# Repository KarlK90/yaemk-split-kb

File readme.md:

<!--
SPDX-FileCopyrightText: 2021 Stefan Kerkmann <karlk90@pm.me>

SPDX-License-Identifier: CC-BY-SA-4.0
-->

# Yet Another Ergonomic Mechanical Keyboard

[![REUSE status](
    https://api.reuse.software/badge/github.com/KarlK90/yaemk-split-kb)](
    https://api.reuse.software/info/github.com/KarlK90/yaemk-split-kb)

# [>>> VISIT THE WEBSITE <<<](https://karlk90.github.io/yaemk-split-kb/)

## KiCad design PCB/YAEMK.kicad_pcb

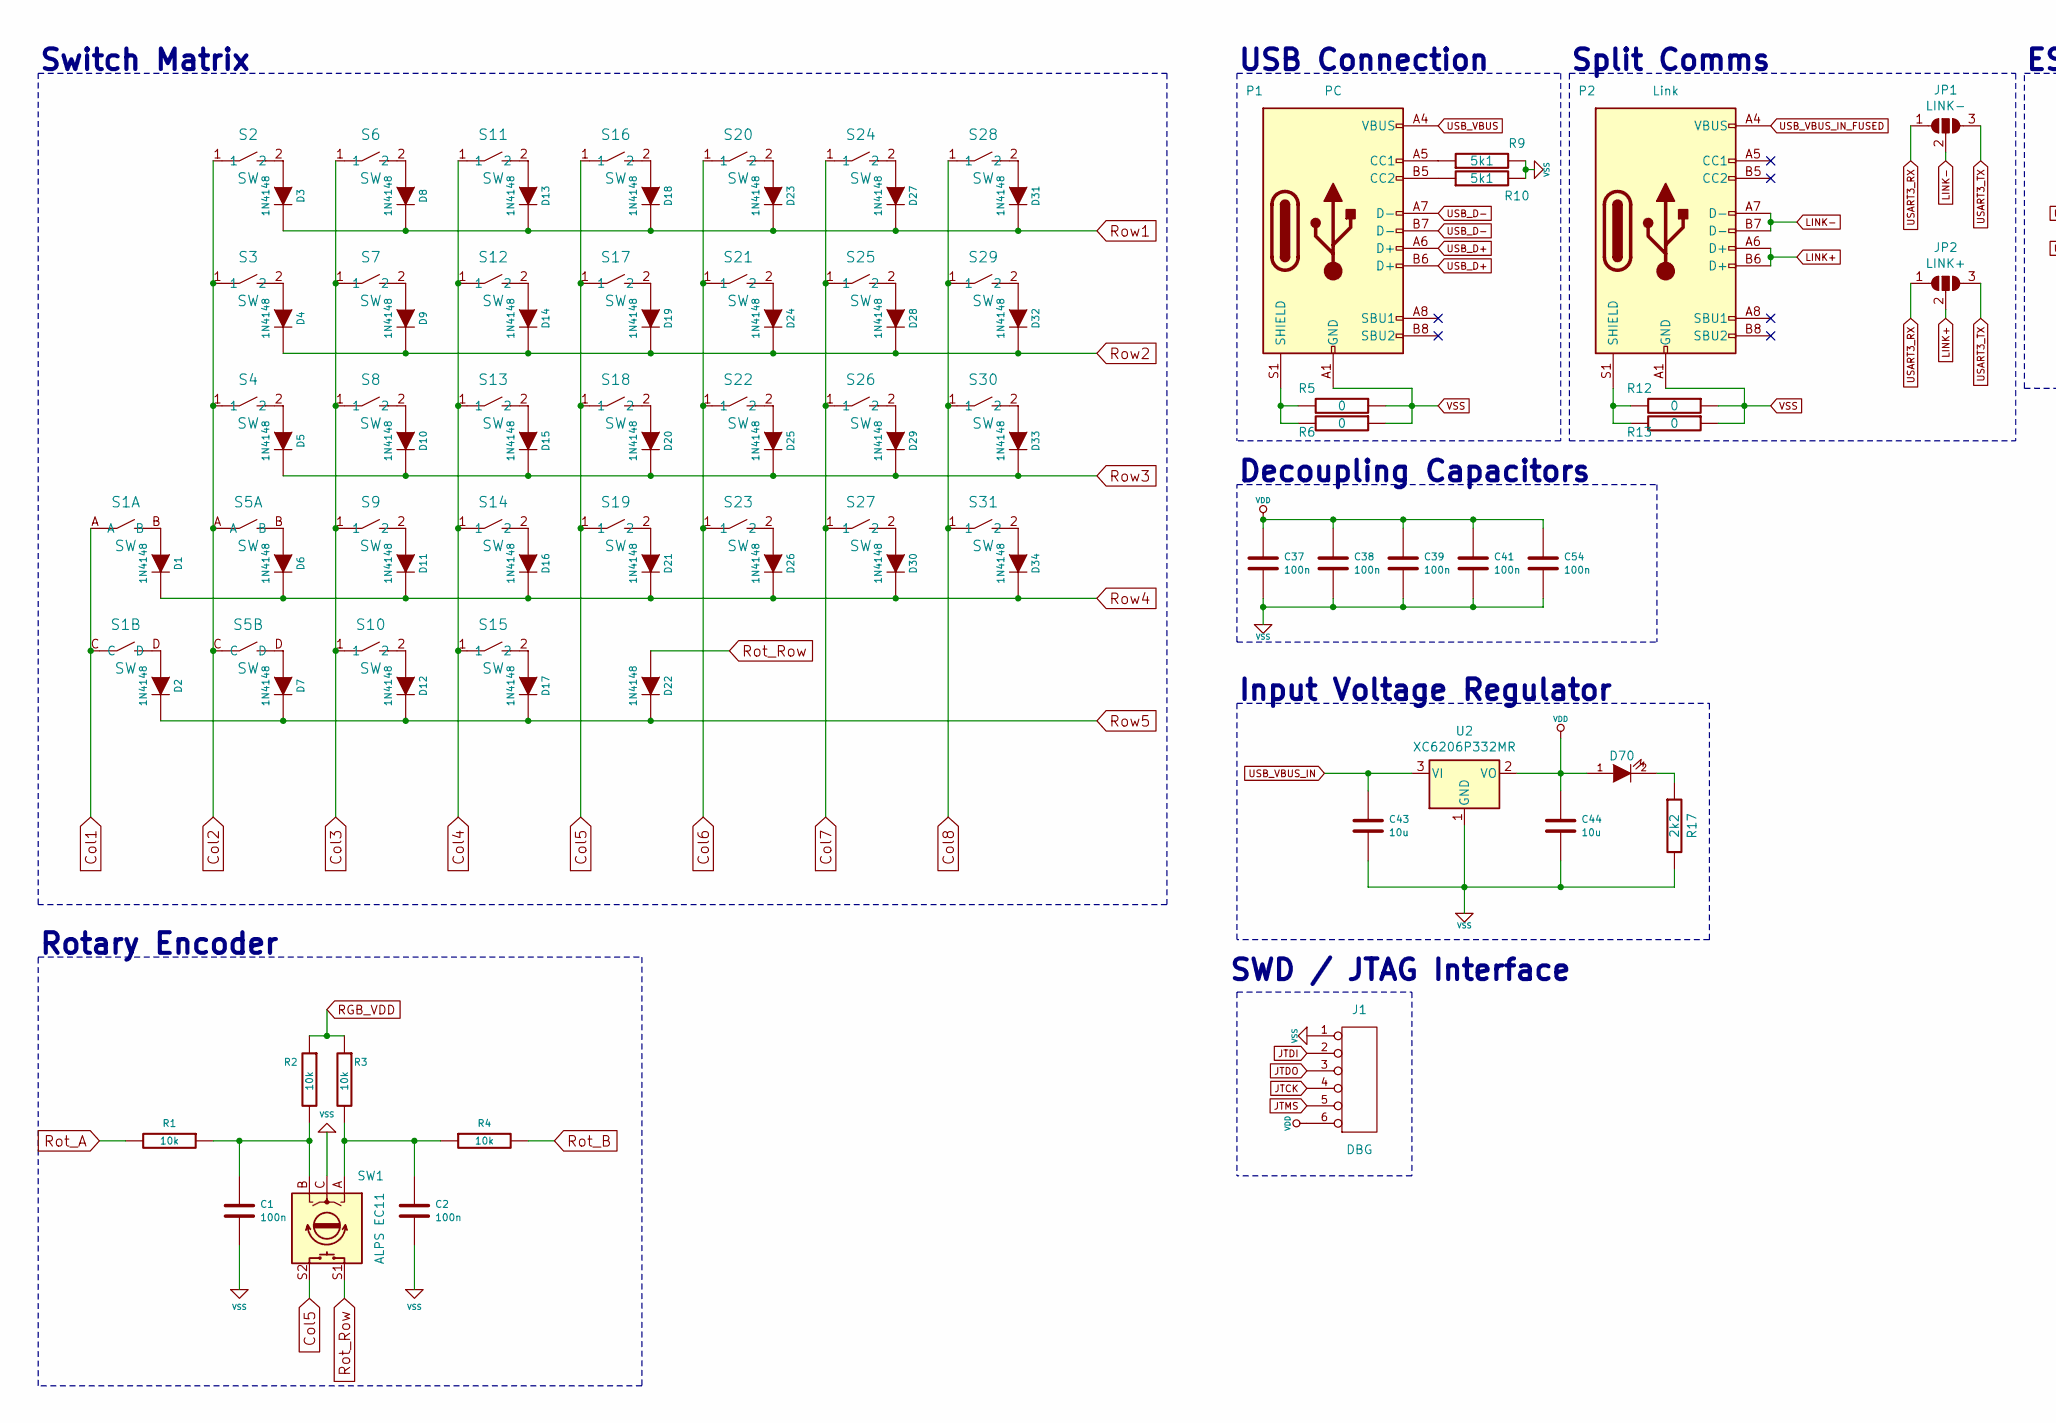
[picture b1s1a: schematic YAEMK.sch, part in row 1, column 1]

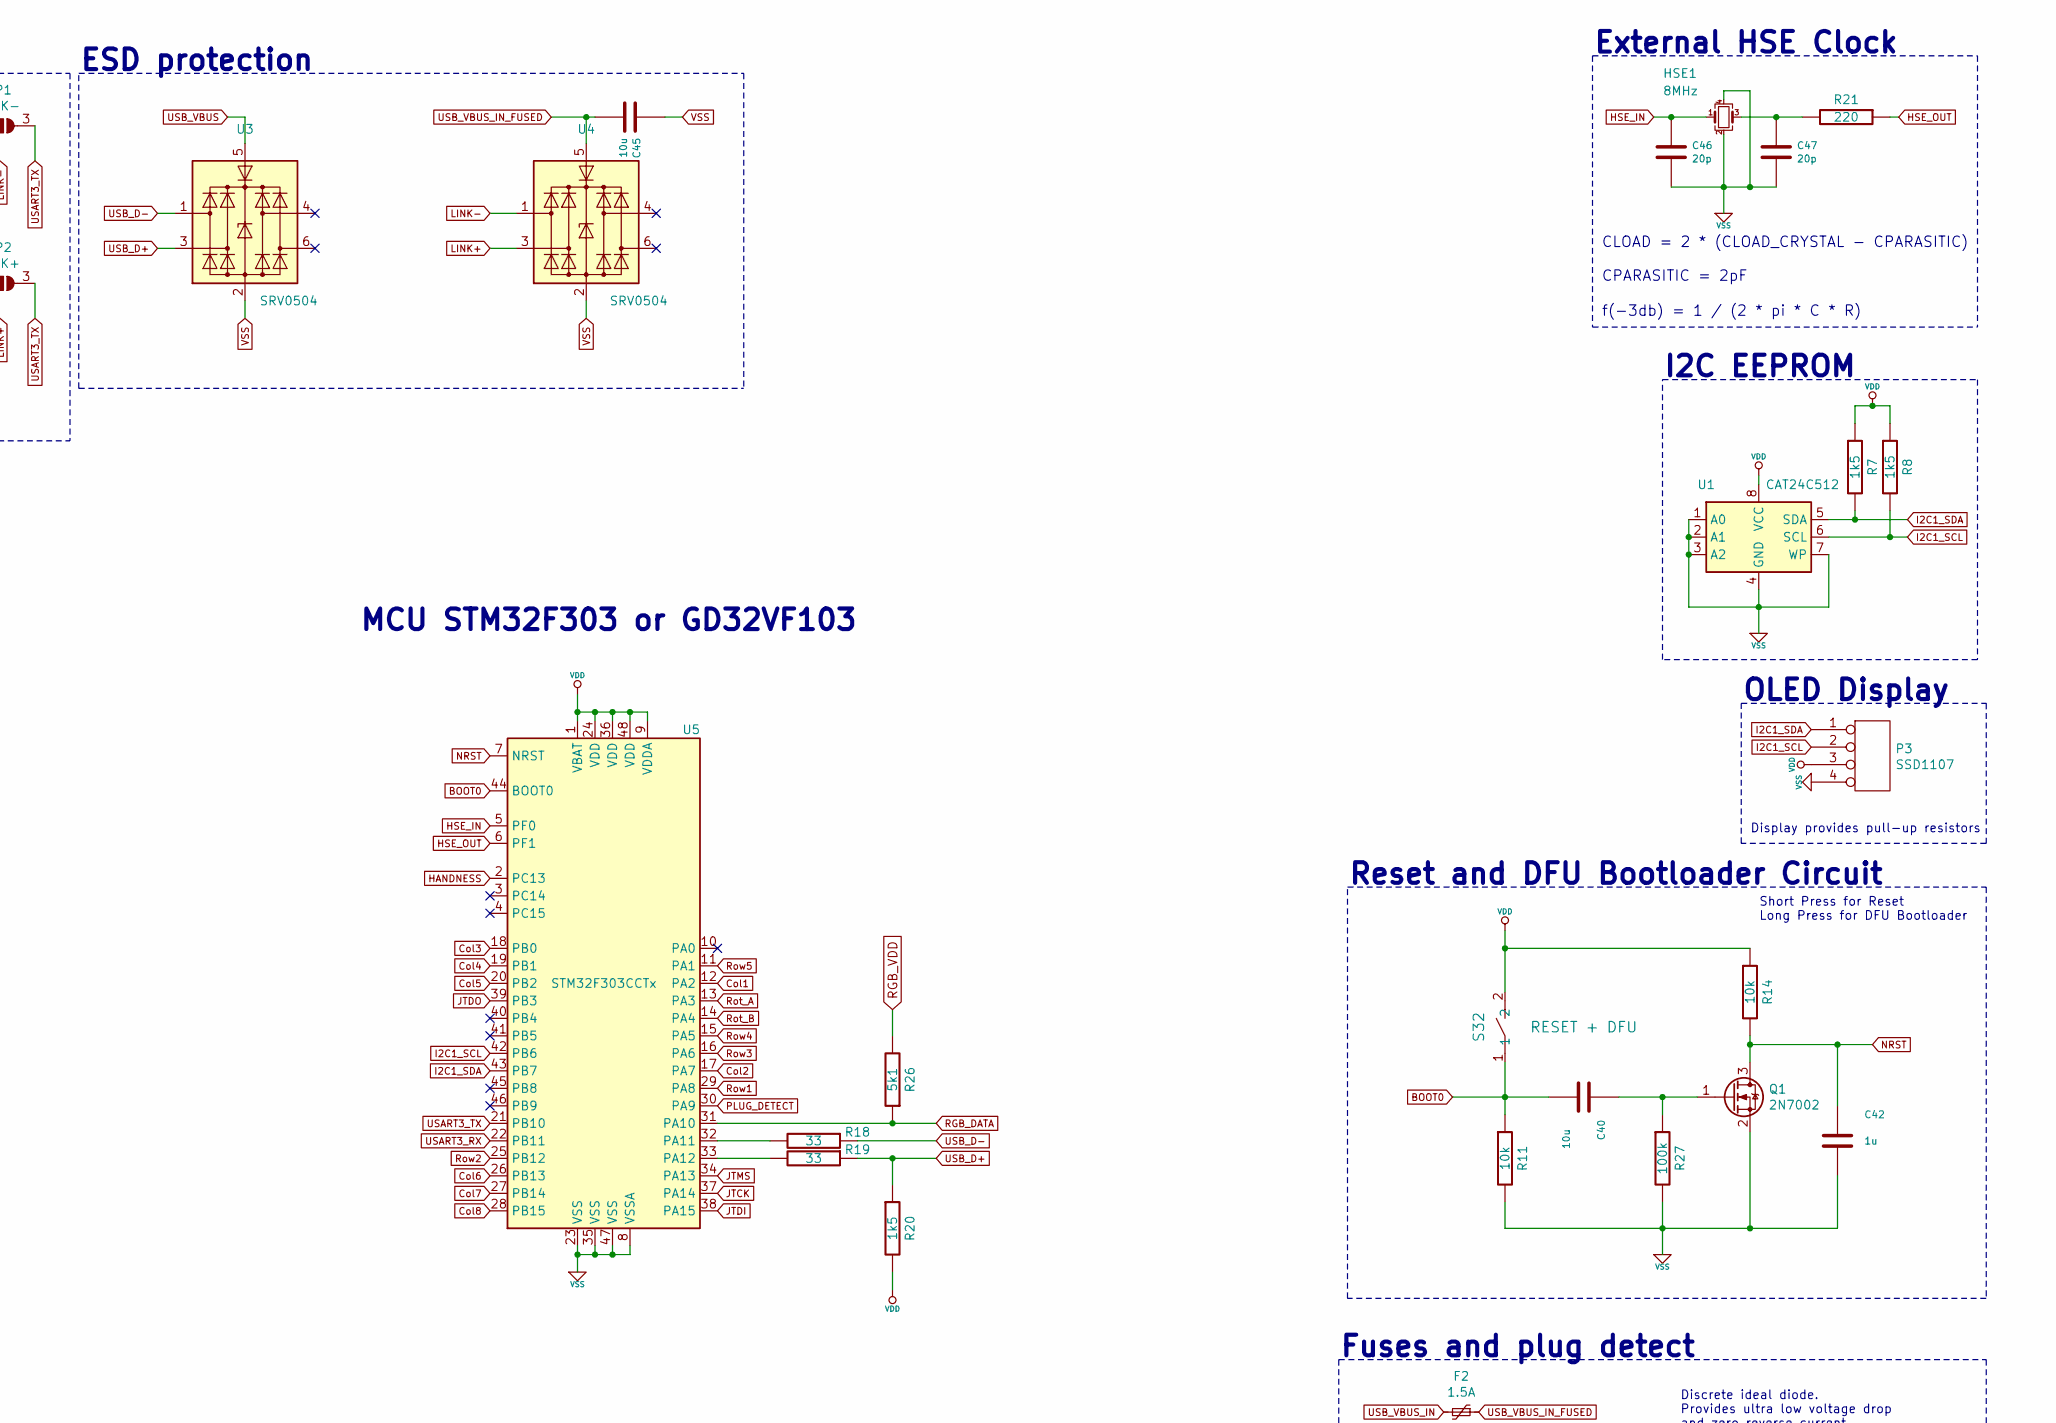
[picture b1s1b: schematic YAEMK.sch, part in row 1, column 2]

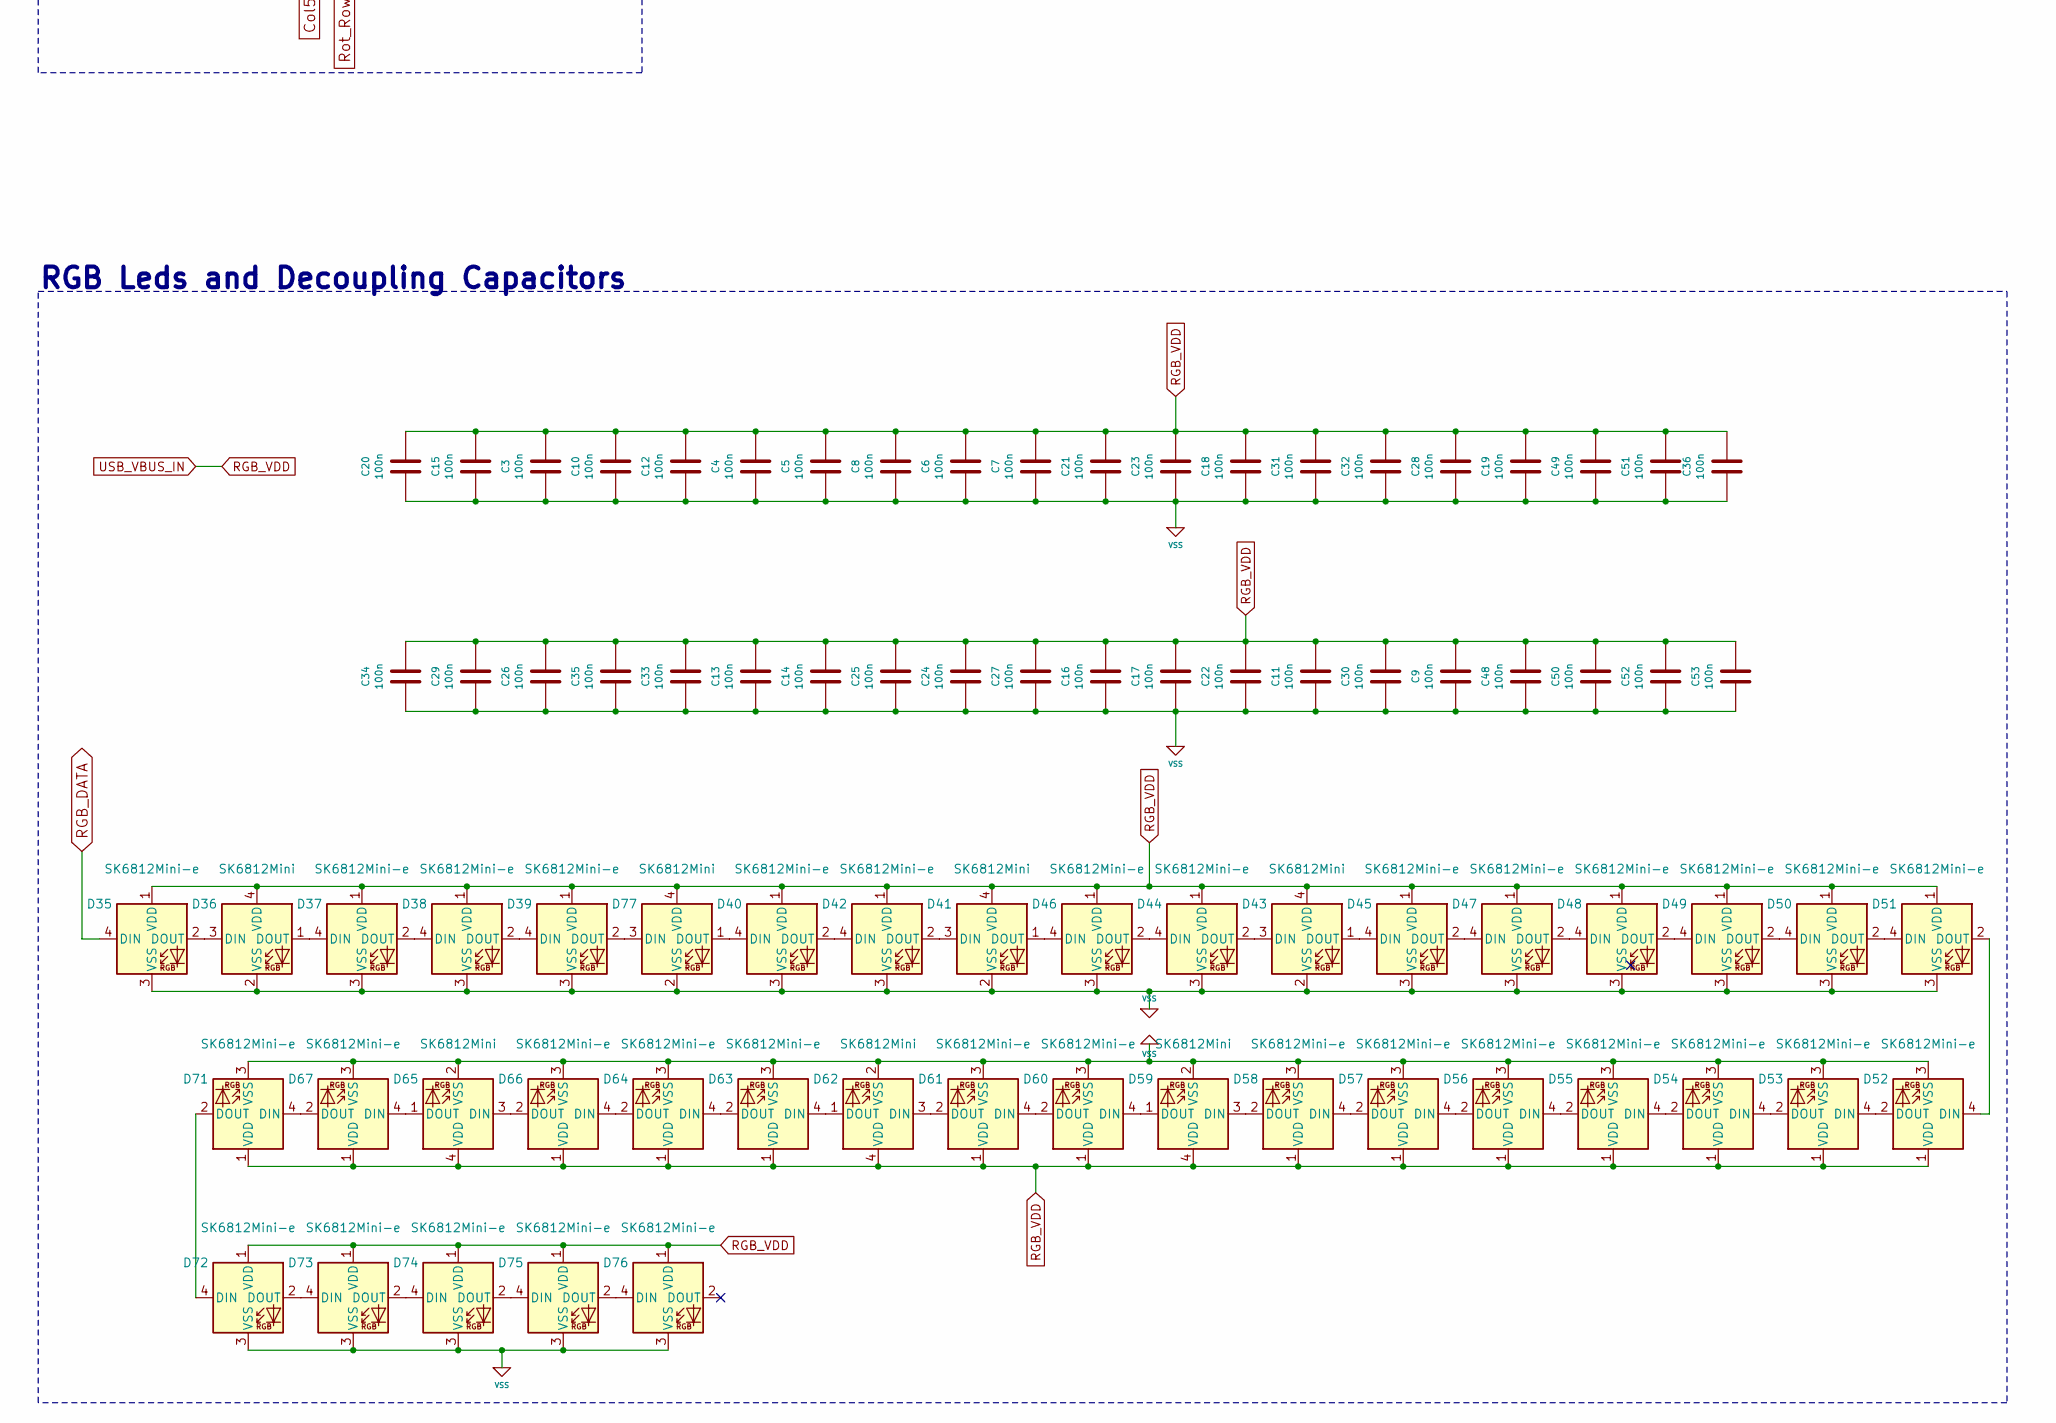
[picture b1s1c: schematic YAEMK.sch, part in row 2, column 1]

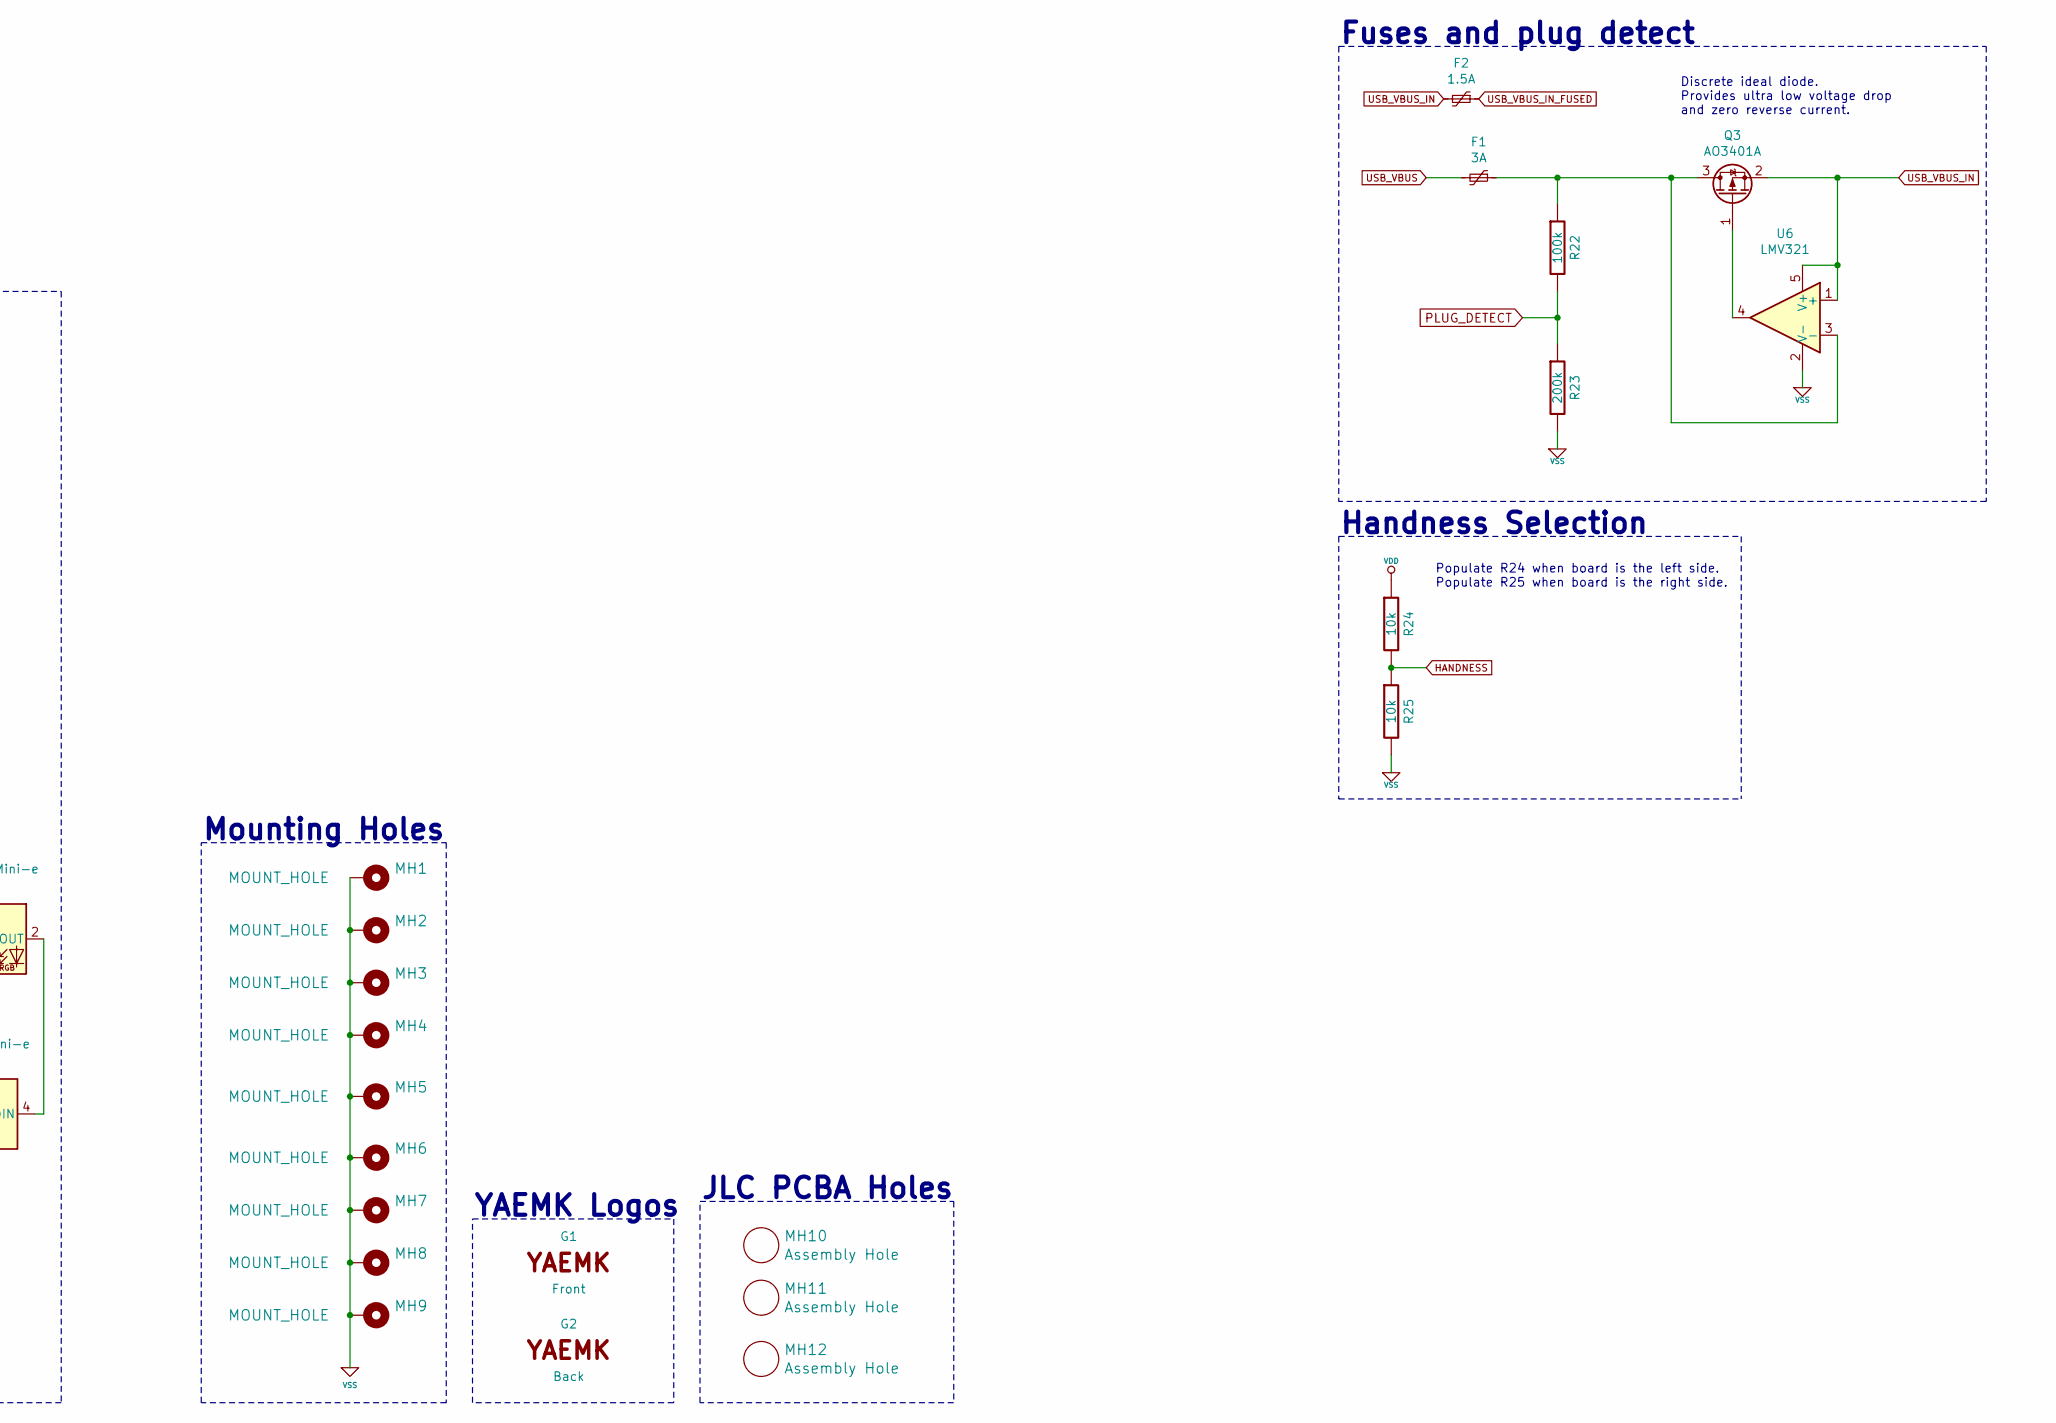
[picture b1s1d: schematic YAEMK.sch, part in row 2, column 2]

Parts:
C1, C2, C3, C4, C5, C6, C7, C8, C9, C10, C11, C12, C13, C14, C15, C16, C17, C18, C19, C20, C21, C22, C23, C24, C25, C26, C27, C28, C29, C30, C31, C32, C33, C34, C35, C36, C37, C38, C39, C41, C48, C49, C50, C51, C52, C53, C54: 100n; SMD-0603; LCSC Part C14663
C40, C43, C44, C45: 10u; SMD-0603; LCSC Part C19702
C42: 1u; SMD-0603; LCSC Part C15849
C46, C47: 20p; SMD-0603; LCSC Part C1648
D1, D2, D3, D4, D5, D6, D7, D8, D9, D10, D11, D12, D13, D14, D15, D16, D17, D18, D19, D20, D21, D22, D23, D24, D25, D26, D27, D28, D29, D30, D31, D32, D33, D34: 1N4148; D_SOD-123; LCSC Part C81598
D35, D37, D38, D39, D40, D42, D44, D45, D46, D47, D48, D49, D50, D51, D52, D53, D54, D55, D56, D57, D58, D60, D61, D63, D64, D66, D67, D71, D72, D73, D74, D75, D76: SK6812Mini-e; SK6812_mini_e_flipable; JLCPCB BOM 0
D36, D41, D43, D59, D62, D65, D77: SK6812Mini; SK6812_mini_flipable; JLCPCB BOM 0
D70: LED; LED-0603_flipable; LCSC Part C268294
F1: 3A; Fuse_1206_3216Metric; LCSC Part C70085
F2: 1.5A; Fuse_1206_3216Metric; LCSC Part C70081
G1: Front; LOGO; JLCPCB BOM 0
G2: Back; LOGO; JLCPCB BOM 0
HSE1: 8MHz; Crystal_SMD_3225-4Pin_3.2x2.5mm; LCSC Part C403948
J1: DBG; PinHeader_1x06_P2.54mm_Horizontal; LCSC Part C376124
JP1: LINK-; SOLDER_JUMPER_3; JLCPCB BOM 0
JP2: LINK+; SOLDER_JUMPER_3; JLCPCB BOM 0
MH1, MH2, MH3, MH4, MH5, MH6, MH7, MH8, MH9: MOUNT_HOLE; MountingHole_2.2mm_M2_Pad_Via; JLCPCB BOM 0
MH10, MH11, MH12: Assembly Hole; JLC_SMT_Assembly_Hole; JLCPCB BOM 0
P1: PC; USB_C_Receptacle_MUP_U22401; LCSC Part C168688
P2: Link; USB_C_Receptacle_MUP_U22401; LCSC Part C168688
P3: SSD1107; SSD1107_DISPLAY; LCSC Part C358718
Q1: 2N7002; SOT-23; LCSC Part C8545
Q3: AO3401A; SOT-23; LCSC Part C15127
R1, R2, R3, R4, R11, R14, R24, R25: 10k; SMD-0603; LCSC Part C25804
R5, R6, R12, R13: 0; SMD-0603; LCSC Part C21189
R7, R8, R20: 1k5; SMD-0603; LCSC Part C22843
R9, R10, R26: 5k1; SMD-0603; LCSC Part C23186
R17: 2k2; SMD-0603; LCSC Part C4190
R18, R19: 33; SMD-0603; LCSC Part C23140
R21: 220; SMD-0603; LCSC Part C22962
R22, R27: 100k; SMD-0603; LCSC Part C25803
R23: 200k; SMD-0603; LCSC Part C25811
S1, S5: SW; MX_KAILH_SOCKET_2U_2X1U; JLCPCB BOM 0
S2, S3, S4, S6, S7, S8, S9, S10, S11, S12, S13, S14, S15, S16, S17, S18, S19, S20, S21, S22, S23, S24, S25, S26, S27, S28, S29, S30, S31: SW; MX_KAILH_SOCKET_1U; JLCPCB BOM 0
S32: RESET + DFU; SMD_Tacticle_Switch_TS24CA_flipable; LCSC Part C393942
SW1: ALPS EC11; RotaryEncoder_Alps_EC11E-Switch_Vertical_H20mm; LCSC Part C370986
U1: CAT24C512; TSSOP-8_4.4x3mm_P0.65mm; LCSC Part C56096
U2: XC6206P332MR; SOT-23; LCSC Part C5446
U3, U4: SRV0504; SOT-23-6; JLCPCB BOM 1
U5: STM32F303CCTx; LQFP-48_7x7mm_P0.5mm; LCSC Part C81523
U6: LMV321; SOT-23-5; JLCPCB BOM 1

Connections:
BOOT0: C40.1, R11.1, S32.1, U5.44 (BOOT0)
Col1: S1.A, S1.C, U5.12 (PA2)
Col2: S2.1, S3.1, S4.1, S5.A, S5.C, U5.17 (PA7)
Col3: S6.1, S7.1, S8.1, S9.1, S10.1, U5.18 (PB0)
Col4: S11.1, S12.1, S13.1, S14.1, S15.1, U5.19 (PB1)
Col5: S16.1, S17.1, S18.1, S19.1, SW1.S2, U5.20 (PB2)
Col6: S20.1, S21.1, S22.1, S23.1, U5.26 (PB13)
Col7: S24.1, S25.1, S26.1, S27.1, U5.27 (PB14)
Col8: S28.1, S29.1, S30.1, S31.1, U5.28 (PB15)
HANDNESS: R24.2, R25.1, U5.2 (PC13)
HSE_IN: C46.1, HSE1.1, U5.5 (PF0)
HSE_OUT: R21.1, U5.6 (PF1)
I2C1_SCL: P3.2, R8.2, U1.6 (SCL), U5.42 (PB6)
I2C1_SDA: P3.1, R7.2, U1.5 (SDA), U5.43 (PB7)
JTCK: J1.4, U5.37 (PA14)
JTDI: J1.2, U5.38 (PA15)
JTDO: J1.3, U5.39 (PB3)
JTMS: J1.5, U5.34 (PA13)
LINK+: JP2.2 (C), P2.A6 (D+), P2.B6 (D+), U4.3 (I/O2)
LINK-: JP1.2 (C), P2.A7 (D-), P2.B7 (D-), U4.1 (I/O1)
NRST: C42.1, Q1.3 (D), R14.2, U5.7 (NRST)
unnamed: C1.1, R1.1, R2.2, SW1.B
unnamed: C2.1, R3.2, R4.1, SW1.A
unnamed: C40.2, Q1.1 (G), R27.1
unnamed: C47.1, HSE1.3, R21.2
unnamed: D1.2 (A), S1.B
unnamed: D2.2 (A), S1.D
unnamed: D3.2 (A), S2.2
unnamed: D4.2 (A), S3.2
unnamed: D5.2 (A), S4.2
unnamed: D6.2 (A), S5.B
unnamed: D7.2 (A), S5.D
unnamed: D8.2 (A), S6.2
unnamed: D9.2 (A), S7.2
unnamed: D10.2 (A), S8.2
unnamed: D11.2 (A), S9.2
unnamed: D12.2 (A), S10.2
unnamed: D13.2 (A), S11.2
unnamed: D14.2 (A), S12.2
unnamed: D15.2 (A), S13.2
unnamed: D16.2 (A), S14.2
unnamed: D17.2 (A), S15.2
unnamed: D18.2 (A), S16.2
unnamed: D19.2 (A), S17.2
unnamed: D20.2 (A), S18.2
unnamed: D21.2 (A), S19.2
unnamed: D23.2 (A), S20.2
unnamed: D24.2 (A), S21.2
unnamed: D25.2 (A), S22.2
unnamed: D26.2 (A), S23.2
unnamed: D27.2 (A), S24.2
unnamed: D28.2 (A), S25.2
unnamed: D29.2 (A), S26.2
unnamed: D30.2 (A), S27.2
unnamed: D31.2 (A), S28.2
unnamed: D32.2 (A), S29.2
unnamed: D33.2 (A), S30.2
unnamed: D34.2 (A), S31.2
unnamed: D35.2 (DOUT), D36.3 (DIN)
unnamed: D36.1 (DOUT), D37.4 (DIN)
unnamed: D37.2 (DOUT), D38.4 (DIN)
unnamed: D38.2 (DOUT), D39.4 (DIN)
unnamed: D39.2 (DOUT), D77.3 (DIN)
unnamed: D40.2 (DOUT), D42.4 (DIN)
unnamed: D40.4 (DIN), D77.1 (DOUT)
unnamed: D41.1 (DOUT), D46.4 (DIN)
unnamed: D41.3 (DIN), D42.2 (DOUT)
unnamed: D43.1 (DOUT), D45.4 (DIN)
unnamed: D43.3 (DIN), D44.2 (DOUT)
unnamed: D44.4 (DIN), D46.2 (DOUT)
unnamed: D45.2 (DOUT), D47.4 (DIN)
unnamed: D47.2 (DOUT), D48.4 (DIN)
unnamed: D48.2 (DOUT), D49.4 (DIN)
unnamed: D49.2 (DOUT), D50.4 (DIN)
unnamed: D50.2 (DOUT), D51.4 (DIN)
unnamed: D51.2 (DOUT), D52.4 (DIN)
unnamed: D52.2 (DOUT), D53.4 (DIN)
unnamed: D53.2 (DOUT), D54.4 (DIN)
unnamed: D54.2 (DOUT), D55.4 (DIN)
unnamed: D55.2 (DOUT), D56.4 (DIN)
unnamed: D56.2 (DOUT), D57.4 (DIN)
unnamed: D57.2 (DOUT), D58.4 (DIN)
unnamed: D58.2 (DOUT), D59.3 (DIN)
unnamed: D59.1 (DOUT), D60.4 (DIN)
unnamed: D60.2 (DOUT), D61.4 (DIN)
unnamed: D61.2 (DOUT), D62.3 (DIN)
unnamed: D62.1 (DOUT), D63.4 (DIN)
unnamed: D63.2 (DOUT), D64.4 (DIN)
unnamed: D64.2 (DOUT), D66.4 (DIN)
unnamed: D65.1 (DOUT), D67.4 (DIN)
unnamed: D65.3 (DIN), D66.2 (DOUT)
unnamed: D67.2 (DOUT), D71.4 (DIN)
unnamed: D70.2 (K), R17.1
unnamed: D71.2 (DOUT), D72.4 (DIN)
unnamed: D72.2 (DOUT), D73.4 (DIN)
unnamed: D73.2 (DOUT), D74.4 (DIN)
unnamed: D74.2 (DOUT), D75.4 (DIN)
unnamed: D75.2 (DOUT), D76.4 (DIN)
unnamed: F1.1, Q3.3 (D), R22.1, U6.3 (-)
unnamed: P1.A5 (CC1), R9.1
unnamed: P1.B5 (CC2), R10.1
unnamed: P1.S1 (SHIELD), R5.2, R6.2
unnamed: P2.S1 (SHIELD), R12.2, R13.2
unnamed: Q3.1 (G), U6.4
unnamed: R18.2, U5.32 (PA11)
unnamed: R19.2, U5.33 (PA12)
PLUG_DETECT: R22.2, R23.1, U5.30 (PA9)
RGB_DATA: D35.4 (DIN), R26.1, U5.31 (PA10)
RGB_VDD: C3.1, C4.1, C5.1, C6.1, C7.1, C8.1, C9.1, C10.1, C11.1, C12.1, C13.1, C14.1, C15.1, C16.1, C17.1, C18.1, C19.1, C20.1, C21.1, C22.1, C23.1, C24.1, C25.1, C26.1, C27.1, C28.1, C29.1, C30.1, C31.1, C32.1, C33.1, C34.1, C35.1, C36.1, C43.1, C48.1, C49.1, C50.1, C51.1, C52.1, C53.1, D35.1 (VDD), D36.4 (VDD), D37.1 (VDD), D38.1 (VDD), D39.1 (VDD), D40.1 (VDD), D41.4 (VDD), D42.1 (VDD), D43.4 (VDD), D44.1 (VDD), D45.1 (VDD), D46.1 (VDD), D47.1 (VDD), D48.1 (VDD), D49.1 (VDD), D50.1 (VDD), D51.1 (VDD), D52.1 (VDD), D53.1 (VDD), D54.1 (VDD), D55.1 (VDD), D56.1 (VDD), D57.1 (VDD), D58.1 (VDD), D59.4 (VDD), D60.1 (VDD), D61.1 (VDD), D62.4 (VDD), D63.1 (VDD), D64.1 (VDD), D65.4 (VDD), D66.1 (VDD), D67.1 (VDD), D71.1 (VDD), D72.1 (VDD), D73.1 (VDD), D74.1 (VDD), D75.1 (VDD), D76.1 (VDD), D77.4 (VDD), F2.2, Q3.2 (S), R2.1, R3.1, R26.2, U2.3 (VI), U6.1 (+), U6.5 (V+)
Rot_A: R1.2, U5.13 (PA3)
Rot_B: R4.2, U5.14 (PA4)
Rot_Row: D22.2 (A), SW1.S1
Row1: D3.1 (K), D8.1 (K), D13.1 (K), D18.1 (K), D23.1 (K), D27.1 (K), D31.1 (K), U5.29 (PA8)
Row2: D4.1 (K), D9.1 (K), D14.1 (K), D19.1 (K), D24.1 (K), D28.1 (K), D32.1 (K), U5.25 (PB12)
Row3: D5.1 (K), D10.1 (K), D15.1 (K), D20.1 (K), D25.1 (K), D29.1 (K), D33.1 (K), U5.16 (PA6)
Row4: D1.1 (K), D6.1 (K), D11.1 (K), D16.1 (K), D21.1 (K), D26.1 (K), D30.1 (K), D34.1 (K), U5.15 (PA5)
Row5: D2.1 (K), D7.1 (K), D12.1 (K), D17.1 (K), D22.1 (K), U5.11 (PA1)
USART3_RX: JP1.1 (A), JP2.1 (A), U5.22 (PB11)
USART3_TX: JP1.3 (B), JP2.3 (B), U5.21 (PB10)
USB_D+: P1.A6 (D+), P1.B6 (D+), R19.1, R20.1, U3.3 (I/O2)
USB_D-: P1.A7 (D-), P1.B7 (D-), R18.1, U3.1 (I/O1)
USB_VBUS: F1.2, P1.A4 (VBUS), P1.A9 (VBUS), P1.B4 (VBUS), P1.B9 (VBUS), U3.5 (VBUS)
USB_VBUS_IN_FUSED: C45.2, F2.1, P2.A4 (VBUS), P2.A9 (VBUS), P2.B4 (VBUS), P2.B9 (VBUS), U4.5 (VBUS)
VDD: C37.1, C38.1, C39.1, C41.1, C44.1, C54.1, D70.1 (A), J1.6, P3.3, R7.1, R8.1, R14.1, R20.2, R24.1, S32.2, U1.8 (VCC), U2.2 (VO), U5.1 (VBAT), U5.9 (VDDA), U5.24 (VDD), U5.36 (VDD), U5.48 (VDD)
VSS: C1.2, C2.2, C3.2, C4.2, C5.2, C6.2, C7.2, C8.2, C9.2, C10.2, C11.2, C12.2, C13.2, C14.2, C15.2, C16.2, C17.2, C18.2, C19.2, C20.2, C21.2, C22.2, C23.2, C24.2, C25.2, C26.2, C27.2, C28.2, C29.2, C30.2, C31.2, C32.2, C33.2, C34.2, C35.2, C36.2, C37.2, C38.2, C39.2, C41.2, C42.2, C43.2, C44.2, C45.1, C46.2, C47.2, C48.2, C49.2, C50.2, C51.2, C52.2, C53.2, C54.2, D35.3 (VSS), D36.2 (VSS), D37.3 (VSS), D38.3 (VSS), D39.3 (VSS), D40.3 (VSS), D41.2 (VSS), D42.3 (VSS), D43.2 (VSS), D44.3 (VSS), D45.3 (VSS), D46.3 (VSS), D47.3 (VSS), D48.3 (VSS), D49.3 (VSS), D50.3 (VSS), D51.3 (VSS), D52.3 (VSS), D53.3 (VSS), D54.3 (VSS), D55.3 (VSS), D56.3 (VSS), D57.3 (VSS), D58.3 (VSS), D59.2 (VSS), D60.3 (VSS), D61.3 (VSS), D62.2 (VSS), D63.3 (VSS), D64.3 (VSS), D65.2 (VSS), D66.3 (VSS), D67.3 (VSS), D71.3 (VSS), D72.3 (VSS), D73.3 (VSS), D74.3 (VSS), D75.3 (VSS), D76.3 (VSS), D77.2 (VSS), HSE1.2, HSE1.4, J1.1, MH1.1, MH2.1, MH3.1, MH4.1, MH5.1, MH6.1, MH7.1, MH8.1, MH9.1, P1.A1 (GND), P1.A12 (GND), P1.B1 (GND), P1.B12 (GND), P2.A1 (GND), P2.A12 (GND), P2.B1 (GND), P2.B12 (GND), P3.4, Q1.2 (S), R5.1, R6.1, R9.2, R10.2, R11.2, R12.1, R13.1, R17.2, R23.2, R25.2, R27.2, SW1.C, U1.1 (A0), U1.2 (A1), U1.3 (A2), U1.4 (GND), U1.7 (WP), U2.1 (GND), U3.2 (GND), U4.2 (GND), U5.8 (VSSA), U5.23 (VSS), U5.35 (VSS), U5.47 (VSS), U6.2 (V-)

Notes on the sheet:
Switch Matrix
Rotary Encoder
Mounting Holes
Split Comms
USB Connection
Decoupling Capacitors
External HSE Clock
CLOAD = 2 * (CLOAD_CRYSTAL - CPARASITIC) CPARASITIC = 2pF
f(-3db) = 1 / (2 * pi * C * R)
SWD / JTAG Interface
Display provides pull-up resistors
OLED Display
Input Voltage Regulator
I2C EEPROM
ESD protection
RGB Leds and Decoupling Capacitors
JLC PCBA Holes
YAEMK Logos
MCU STM32F303 or GD32VF103
Populate R24 when board is the left side. Populate R25 when board is the right side.
Handness Selection
Discrete ideal diode. Provides ultra low voltage drop and zero reverse current.
Fuses and plug detect
Reset and DFU Bootloader Circuit
Short Press for Reset Long Press for DFU Bootloader

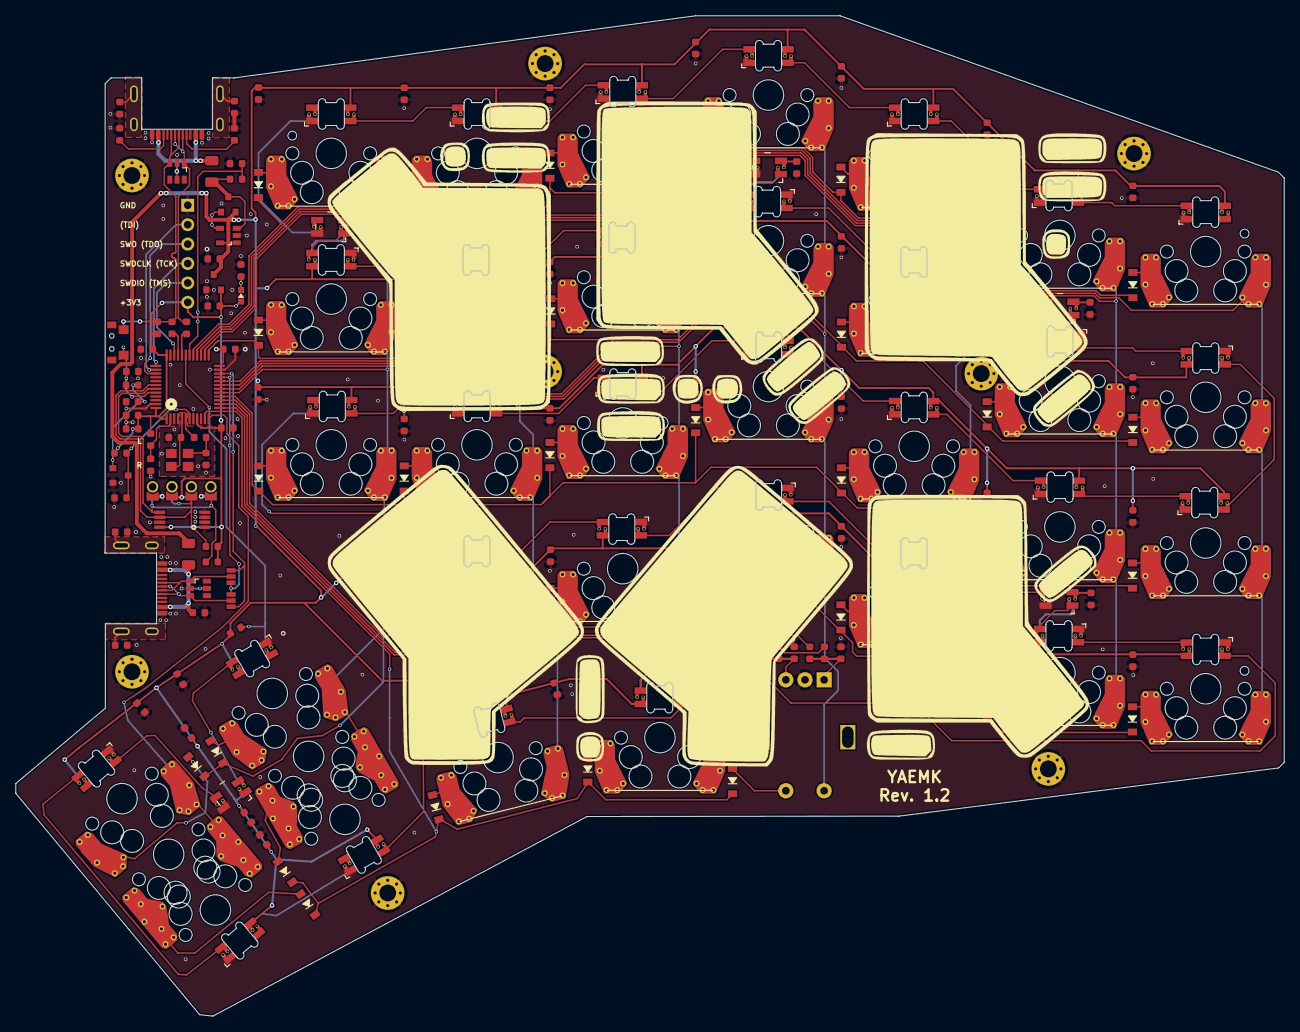
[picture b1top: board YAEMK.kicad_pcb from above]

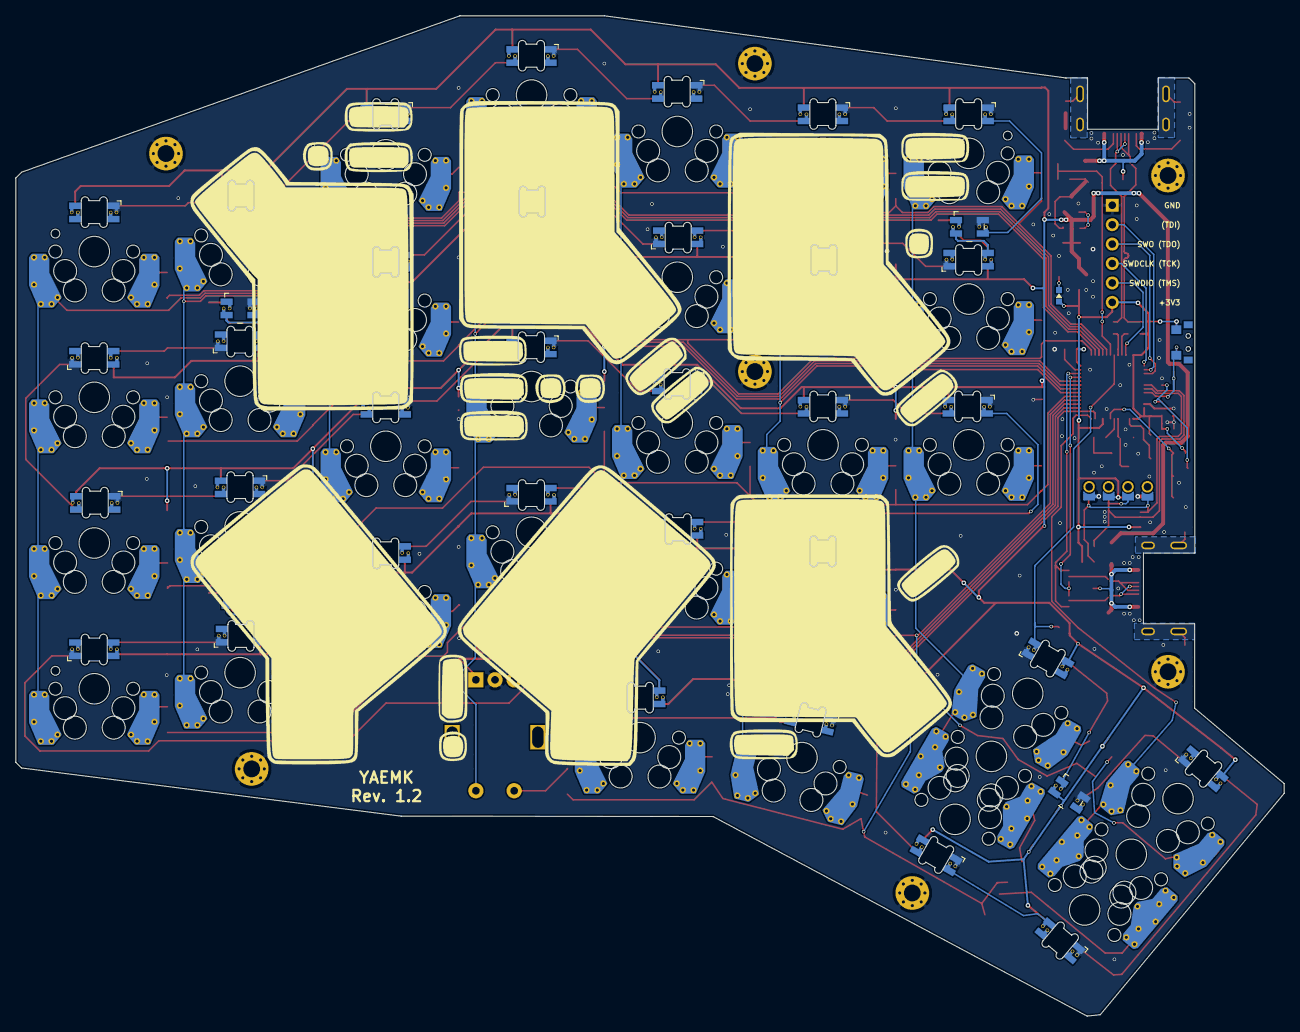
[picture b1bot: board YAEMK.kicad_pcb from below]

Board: 2 copper layers, 165.8 x 130.8 mm, 218 parts (3 on the bottom side), 125 nets.

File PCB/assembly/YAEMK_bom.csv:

100n ,"C1,C2,C39,C38,C41,C37,C54,C53,C50,C51,C49,C52,C48,C24,C7,C3,C4,C5,C6,C19,C8,C10,C9,C14,C11,C12,C22,C16,C17,C18,C15,C13,C20,C28,C21,C23,C25,C27,C30,C29,C26,C32,C33,C34,C31,C35,C36",SMD-0603, C14663
1u ,C42,SMD-0603, C15849
10u ,"C43,C44,C45,C40",SMD-0603,C19702
20p ,"C46,C47",SMD-0603, C1648
1N4148 ,"D8,D13,D18,D23,D27,D31,D4,D9,D14,D19,D24,D28,D32,D10,D15,D20,D25,D29,D33,D1,D6,D11,D16,D21,D26,D30,D34,D2,D7,D12,D17,D5,D22,D3",D_SOD-123, C81598
"3A Resettable fuse, polymeric positive temperature coefficient, small symbol",F1,Fuse_1206_3216Metric,C70085
"1.5A Resettable fuse, polymeric positive temperature coefficient, small symbol",F2,Fuse_1206_3216Metric,C70081
"8MHz Four pin crystal, GND on pins 2 and 4, small symbol",HSE1,Crystal_SMD_3225-4Pin_3.2x2.5mm, C403948
"2N7002 0.115A Id, 60V Vds, N-Channel MOSFET, SOT-23",Q1,SOT-23, C8545
"AO3401A -0.18A Id, -60V Vds, P-Channel MOSFET, SOT-23",Q3,SOT-23, C15127
10k ,"R1,R4,R2,R3,R24,R25,R11,R14",SMD-0603, C25804
0 ,"R13,R12,R6,R5",SMD-0603, C21189
2k2 ,R17,SMD-0603, C4190
33 ,"R18,R19",SMD-0603, C23140
1k5 ,"R20,R8,R7",SMD-0603, C22843
220 ,R21,SMD-0603, C22962
100k ,"R22,R27",SMD-0603, C25803
200k ,R23,SMD-0603, C25811
5k1 ,"R9,R10,R26",SMD-0603, C23186
"CAT24C512 I2C Serial EEPROM, 16Kb, DIP-8/SOIC-8/TSSOP-8/DFN-8",U1,TSSOP-8_4.4x3mm_P0.65mm,C56096
XC6206P332MR ,U2,SOT-23,C5446
"SRV0504 Very low capacitance ESD protection diode, 4 data-line, SOT-23-6","U3,U4",SOT-23-6, C384888
"STM32F303CCTx ARM Cortex-M4 MCU, 128KB flash, 32KB RAM, 72MHz, 2-3.6V, 37 GPIO, LQFP-48",U5,LQFP-48_7x7mm_P0.5mm, C81523
"LMV321 Low-Voltage Rail-to-Rail Output Operational Amplifiers, SOT-23-5/SC-70-5",U6,SOT-23-5, C90297

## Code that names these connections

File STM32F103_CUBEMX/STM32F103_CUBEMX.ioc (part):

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Mcu.Name=STM32F103C(8-B)Tx
Mcu.Package=LQFP48
Mcu.UserName=STM32F103CBTx
PA10.GPIOParameters=GPIO_Label
PA10.GPIO_Label=Row1
PA10.Signal=GPIO_Input
PA11.Mode=Device
PA11.Signal=USB_DM
PA12.Mode=Device
PA12.Signal=USB_DP
PA13.Mode=JTAG_4_pins
PA13.Signal=SYS_JTMS-SWDIO
PA14.Mode=JTAG_4_pins
PA14.Signal=SYS_JTCK-SWCLK
PA15.Mode=JTAG_4_pins
PA15.Signal=SYS_JTDI
PA4.GPIOParameters=GPIO_Label
PA4.GPIO_Label=Row4
PA4.Signal=GPIO_Input
PA5.GPIOParameters=GPIO_Label
PA5.GPIO_Label=Row5
PA5.Signal=GPIO_Input
PA6.GPIOParameters=GPIO_Label
PA6.GPIO_Label=Row3
PA6.Signal=GPIO_Input
PA7.GPIOParameters=GPIO_Label
PA7.GPIO_Label=Rot_B
PA7.Signal=GPIO_Input
PA8.GPIOParameters=GPIO_Label
PA8.GPIO_Label=Col8
PA8.Signal=GPIO_Output
PA9.GPIOParameters=GPIO_Label
PA9.GPIO_Label=Col6
PA9.Signal=GPIO_Output
PB0.GPIOParameters=GPIO_Label
PB0.GPIO_Label=Rot_A
PB0.Signal=GPIO_Input
PB1.GPIOParameters=GPIO_Label
PB1.GPIO_Label=Col2
PB1.Signal=GPIO_Output
PB10.Mode=Asynchronous
PB10.Signal=USART3_TX
PB11.Mode=Asynchronous
PB11.Signal=USART3_RX
PB12.Signal=GPIO_Input
PB13.Mode=Simplex_Bidirectional_Master
PB13.Signal=SPI2_SCK
PB14.GPIOParameters=GPIO_Label
PB14.GPIO_Label=Row2
PB14.Signal=GPIO_Input
PB15.Mode=Simplex_Bidirectional_Master
PB15.Signal=SPI2_MOSI
PB2.Signal=GPIO_Output
PB3.Mode=JTAG_4_pins
PB3.Signal=SYS_JTDO-TRACESWO
PB5.GPIOParameters=GPIO_Label
PB5.GPIO_Label=MCU_LED
PB5.Signal=GPIO_Output
PB6.Mode=I2C
PB6.Signal=I2C1_SCL
PB7.Mode=I2C
PB7.Signal=I2C1_SDA
PD0-OSC_IN.Mode=HSE-External-Oscillator
PD0-OSC_IN.Signal=RCC_OSC_IN
PD1-OSC_OUT.Mode=HSE-External-Oscillator
PD1-OSC_OUT.Signal=RCC_OSC_OUT
RCC.SYSCLKFreq_VALUE=72000000
RCC.SYSCLKSource=RCC_SYSCLKSOURCE_PLLCLK
board=custom
